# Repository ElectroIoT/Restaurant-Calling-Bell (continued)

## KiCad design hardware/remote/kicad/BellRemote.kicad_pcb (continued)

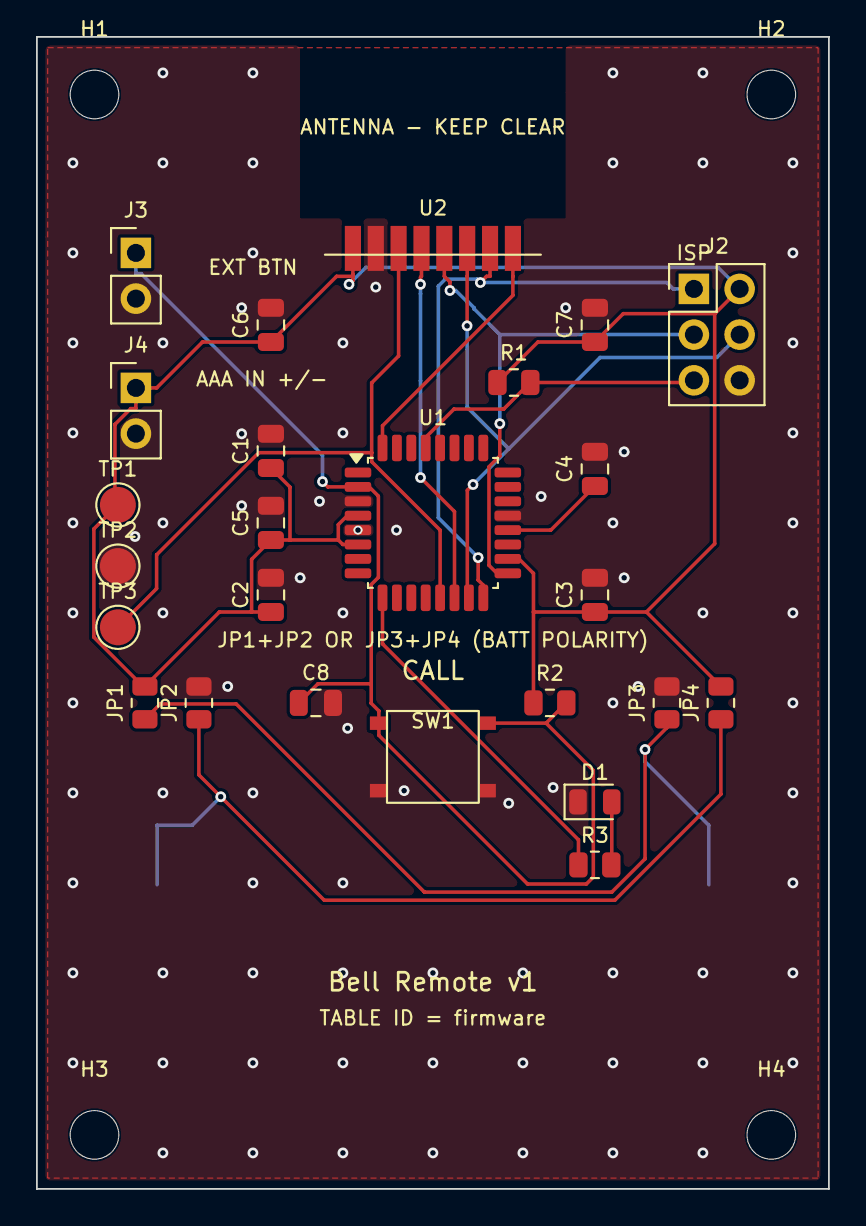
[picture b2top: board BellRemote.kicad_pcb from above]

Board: 2 copper layers, 44.0 x 64.0 mm, 30 parts (1 on the bottom side), 15 nets.

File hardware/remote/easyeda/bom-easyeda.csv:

Designator,Footprint,Quantity,Value,Manufacturer Part,Manufacturer,Supplier Part,Supplier
BT1,CR2450_Holder_MY-2450-01,1,CR2450,MY-2450-01,MYOUNG,C964845,LCSC
"C1,C2,C3,C4,C6",C_0805_2012Metric,5,100nF,CL21B104KBCNNNC,Samsung,C1711,LCSC
C5,C_0805_2012Metric,1,10uF,CL21A106KAYNNNE,Samsung,C15850,LCSC
C7,C_0805_2012Metric,1,22uF,CL21A226MQQNNNE,Samsung,C5674,LCSC
C8,C_0805_2012Metric,1,10nF,CL21B103KBANNNC,Samsung,C1710,LCSC
D1,LED_0805_2012Metric,1,red,KT-0805R,Hubei KENTO,C2295,LCSC
J2,PinHeader_2x03_P2.54mm_Vertical,1,ISP,PZ254V-12-06P-T,XFCN,C56153599,LCSC
J3,PinHeader_1x02_P2.54mm_Vertical,1,EXT BUTTON,PZ254V-11-02P,XFCN,C492401,LCSC
J4,PinHeader_1x02_P2.54mm_Vertical,1,2xAAA IN (+ / -),PZ254V-11-02P,XFCN,C492401,LCSC
"JP1,JP2,JP3,JP4",R_0805_2012Metric,4,0R,0805W8F0000T5E,UNI-ROYAL,C17477,LCSC
R1,R_0805_2012Metric,1,10k,0805W8F1002T5E,UNI-ROYAL,C17414,LCSC
R2,R_0805_2012Metric,1,470k,0805W8F4703T5E,UNI-ROYAL,C17709,LCSC
R3,R_0805_2012Metric,1,1k,0805W8F1001T5E,UNI-ROYAL,C17513,LCSC
SW1,SW_TS-1187A,1,CALL,TS-1187A-B-A-B,XKB Connection,C318884,LCSC
U1,TQFP-32_7x7mm_P0.8mm,1,ATmega328P-AU,ATMEGA328P-AU,Microchip,C14877,LCSC

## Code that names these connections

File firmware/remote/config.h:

/*
 * config.h - build-time configuration of the table remote.
 *
 * Override any value with a compiler flag, e.g.
 *   arduino-cli compile ... --build-property "build.extra_flags=-DTABLE_ID=7"
 * (see docs/flashing-guide.md and tools/build_remotes.py, which builds all ten).
 */
#ifndef REMOTE_CONFIG_H
#define REMOTE_CONFIG_H

#include <Arduino.h>
#include "radio_driver.h"

/* ---- identity ---------------------------------------------------------------------- */
#ifndef TABLE_ID
#define TABLE_ID 1                 /* 1..10 */
#endif
static_assert(TABLE_ID >= 1 && TABLE_ID <= 10, "TABLE_ID must be 1..10");

/* ---- board ------------------------------------------------------------------------- */
/* 0 = Arduino Uno prototype (16 MHz, 5 V logic: use a 3.3 V radio supply and 4.7k series
 *     resistors on SCK/MOSI/CSN/CE, see docs/wiring.md)
 * 1 = custom remote PCB: ATmega328P-AU, 3 V coin cell, 4 MHz (8 MHz RC with CKDIV8 fuse,
 *     firmware switches the prescaler to /2). ATmega328P is only rated for 4 MHz below 2.7 V. */
#ifndef BELL_BOARD_PCB
#define BELL_BOARD_PCB 0
#endif
#if BELL_BOARD_PCB && (F_CPU != 4000000UL)
#error "Custom remote PCB build must use F_CPU=4000000 (build.f_cpu=4000000L), see docs/flashing-guide.md"
#endif

/* ---- pins (same on Uno prototype and PCB) ------------------------------------------- */
#define PIN_RADIO_CE    9          /* PB1 */
#define PIN_RADIO_CSN   10         /* PB2 */
#define PIN_BUTTON      4          /* PD4 = PCINT20, active low */
#define PIN_LED         5          /* PD5, active high through series resistor */
#define PIN_RADIO_IRQ   2          /* PD2, wired but unused: STATUS is polled */

/* Custom PCB has a 470k external pull-up so a stuck button draws ~6 uA instead of ~100 uA
 * through the internal pull-up. Uno prototype uses the internal pull-up. */
#ifndef BUTTON_EXTERNAL_PULLUP
#define BUTTON_EXTERNAL_PULLUP BELL_BOARD_PCB
#endif

/* ---- radio ------------------------------------------------------------------------- */
#ifndef BELL_CHANNEL
#define BELL_CHANNEL 76            /* 2476 MHz: above Wi-Fi channels 1/6/11, inside 2400-2483.5 */
#endif
static_assert(BELL_CHANNEL <= 83, "channel above 2483 MHz is outside the ISM band in many countries");
#ifndef BELL_RATE
#define BELL_RATE RADIO_RATE_250K  /* best sensitivity (-96 dBm); airtime ~0.55 ms per frame */
#endif
#ifndef BELL_TX_POWER
#define BELL_TX_POWER RADIO_PWR_0DBM  /* 0 dBm = 12 mA TX; coin-cell friendly. +4 dBm = 16 mA. */
#endif
#define BELL_HW_RETRY_DELAY  3     /* ARD code: (3+1)*250 = 1000 us, must exceed the ACK airtime */
#define BELL_HW_RETRY_COUNT  3     /* hardware retransmissions per transmit */
static_assert(BELL_RATE != RADIO_RATE_250K || BELL_HW_RETRY_DELAY >= 1, "ARD too short for 250 kbps");

/* ---- application retry ------------------------------------------------------------- */
#define CALL_MAX_ATTEMPTS        8
#define CALL_REPLY_TIMEOUT_MS    40      /* wait for CALL_ACCEPTED after the radio ACK */
#define CALL_BACKOFF_BASE_MS     60
#define CALL_BACKOFF_JITTER_MS   120     /* + 0..119 ms pseudo-random, spreads simultaneous remotes */
static_assert(CALL_MAX_ATTEMPTS >= 1 && CALL_MAX_ATTEMPTS <= 30, "attempts out of range");

/* ---- served notification (poll) ---------------------------------------------------- */
/* After a call is accepted the remote cannot listen continuously (RX = 14 mA). It instead
 * wakes every 8 s and asks "is my call served?" for a limited window, then sleeps for good. */
#ifndef SERVED_POLL_ENABLE
#define SERVED_POLL_ENABLE 1
#endif
#define SERVED_POLL_WINDOW_S     300     /* give up after 5 minutes */
#define SERVED_POLL_PERIOD_S     8       /* fixed by the watchdog timeout */

/* ---- user interface timing ---------------------------------------------------------- */
#define BUTTON_DEBOUNCE_MS       30
#define BUTTON_LOCKOUT_MS        1500    /* ignore further presses after a call */
#define BUTTON_STUCK_MS          30000   /* a button held this long is treated as stuck */
#define LED_WAIT_PERIOD_MS       100     /* fast flash while waiting for acknowledgement */
#define LED_SUCCESS_MS           1000    /* solid */
#define LED_ERROR_FLASHES        5       /* rapid flashes on failure */

/* ---- battery ----------------------------------------------------------------------- */
#ifndef LOW_BATT_MV
#define LOW_BATT_MV 2400           /* below this the low-battery flag is sent and LED blips */
#endif
#ifndef BELL_DEBUG_SERIAL
#define BELL_DEBUG_SERIAL 0        /* Uno prototype only; leave 0 on the PCB */
#endif
#if BELL_DEBUG_SERIAL && BELL_BOARD_PCB
#error "Serial debug is for the Uno prototype only"
#endif

#endif
